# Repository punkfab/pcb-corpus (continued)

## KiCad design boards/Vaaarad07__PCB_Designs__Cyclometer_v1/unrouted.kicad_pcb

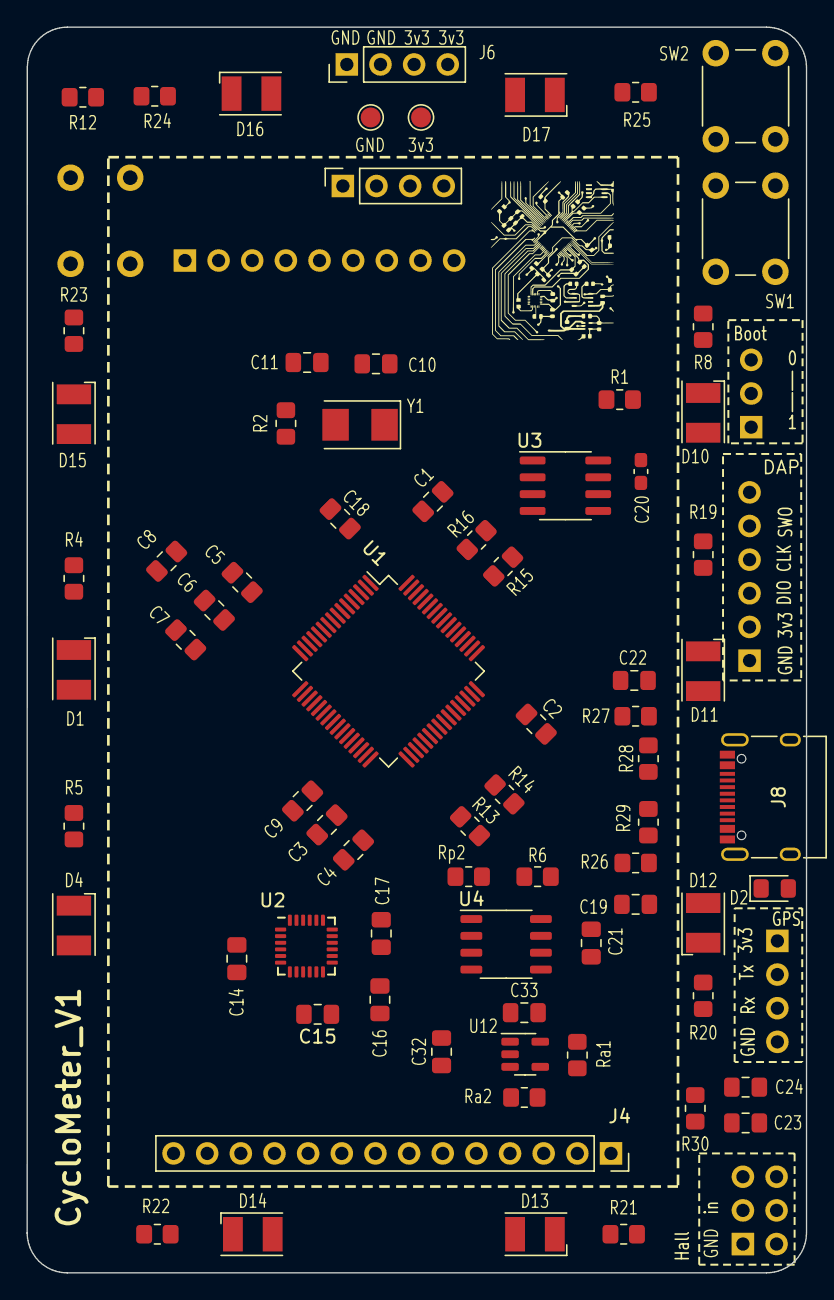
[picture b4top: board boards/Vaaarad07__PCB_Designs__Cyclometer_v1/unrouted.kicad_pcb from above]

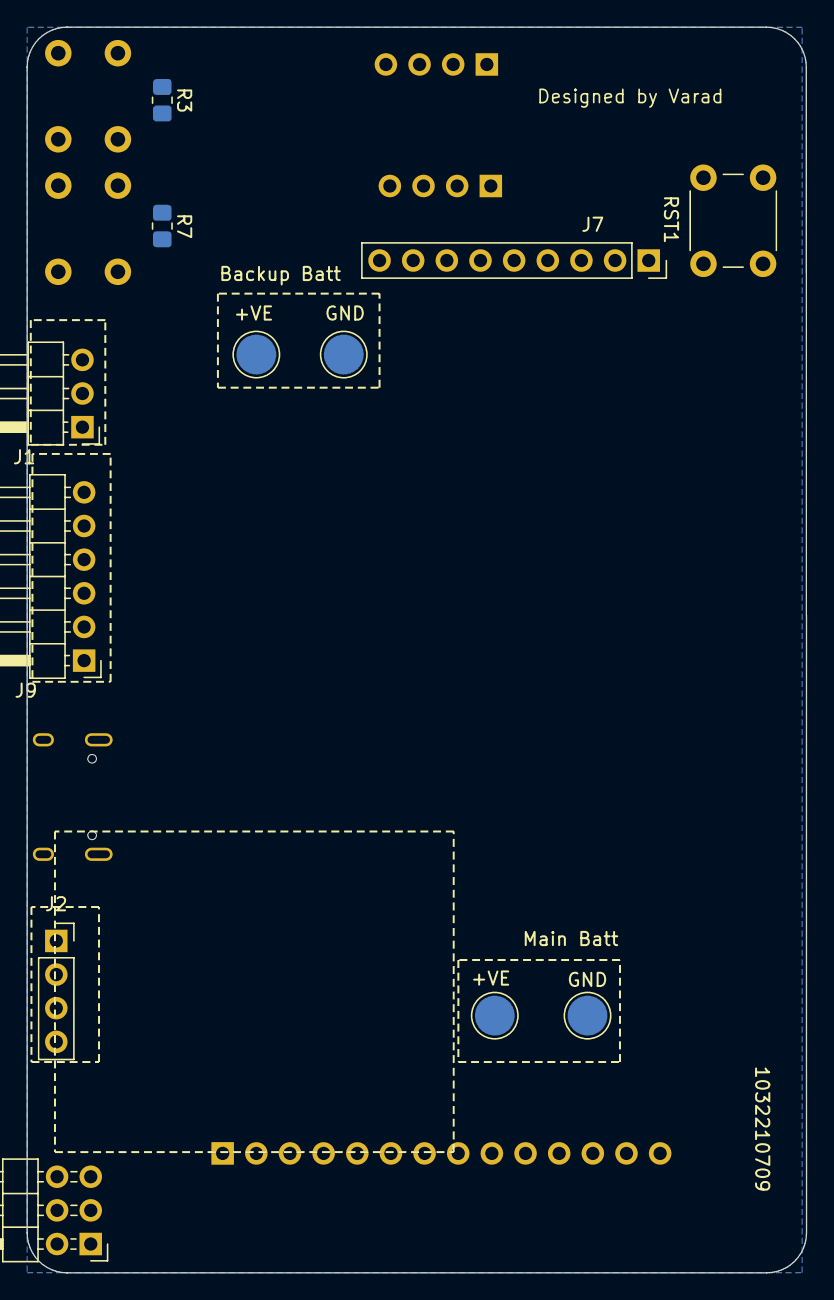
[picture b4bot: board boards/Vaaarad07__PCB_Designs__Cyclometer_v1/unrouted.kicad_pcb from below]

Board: 2 copper layers, 58.8 x 94.0 mm, 87 parts (12 on the bottom side), 66 nets, no tracks yet.

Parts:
C1, C2, C3, C4, C5, C6, C8: 100nF; C_0805_2012Metric_Pad1.18x1.45mm_HandSolder
C7: 1uF; C_0805_2012Metric_Pad1.18x1.45mm_HandSolder
C9: 4.7uF; C_0805_2012Metric_Pad1.18x1.45mm_HandSolder
C10, C11: TBC; C_0805_2012Metric_Pad1.18x1.45mm_HandSolder
C14: 10nF; C_0805_2012Metric_Pad1.18x1.45mm_HandSolder
C15, C16, C19, C24: 0.1uF; C_0805_2012Metric_Pad1.18x1.45mm_HandSolder
C17: 2.2nF; C_0805_2012Metric_Pad1.18x1.45mm_HandSolder
C18, C21, C22, C23, C32, C33: 10uF; C_0805_2012Metric_Pad1.18x1.45mm_HandSolder
C20: 100nF; C_0603_1608Metric_Pad1.08x0.95mm_HandSolder
D1, D4, D10, D11, D12, D13, D14, D15, D16, D17: LED; LED_PLCC-2_3.4x3.0mm_KA
D2: LED; LED_0805_2012Metric_Pad1.15x1.40mm_HandSolder
J1: Conn_01x03_Male; PinHeader_1x03_P2.54mm_Horizontal
J2: GPS; PinSocket_1x04_P2.54mm_Vertical
J3: Conn_01x06_Pin; PinHeader_2x03_P2.54mm_Horizontal
J4: LCD; PinSocket_1x14_P2.54mm_Vertical
J5: LCD; PinSocket_1x04_P2.54mm_Vertical
J6: PinHeader_1x04_P2.54mm_Vertical
J7: NRF; PinSocket_1x09_P2.54mm_Vertical
J8: USB_C_Receptacle; USB_C_Receptacle_XKB_U262-16XN-4BVC11
J9: Conn_01x06_Pin; PinHeader_1x06_P2.54mm_Horizontal
R1, R3, R4, R5, R7, R8, R12, R19, R20, R21, R22, R23, R24, R25, R30: 10K; R_0805_2012Metric_Pad1.20x1.40mm_HandSolder
R2: TBC; R_0805_2012Metric_Pad1.20x1.40mm_HandSolder
R6: R_Small_US; R_0805_2012Metric_Pad1.20x1.40mm_HandSolder
R13, R14, R15, R16: 4.7k; R_0805_2012Metric_Pad1.20x1.40mm_HandSolder
R26, R27, R28, R29: 5.1k; R_0805_2012Metric_Pad1.20x1.40mm_HandSolder
RST1: SW_Push; SW_PUSH_6mm
Ra1, Ra2: R_Small_US; R_0805_2012Metric_Pad1.20x1.40mm_HandSolder
Rp2: 1K2; R_0805_2012Metric_Pad1.20x1.40mm_HandSolder
SW1, SW2: SW_Push; SW_PUSH_6mm
TP1, TP4: +VE; TestPoint_Pad_D3.0mm
TP2, TP3: GND; TestPoint_Pad_D3.0mm
TP5: GND; TestPoint_Pad_D1.5mm
TP6: 3v3; TestPoint_Pad_D1.5mm
U1: STM32F446RCTx; LQFP-64_10x10mm_P0.5mm
U2: MPU-6050; InvenSense_QFN-24_4x4mm_P0.5mm
U3: AT24CS32-SSHM; SOIC-8_3.9x4.9mm_P1.27mm
U4: TP4056; SOP-8_3.9x4.9mm_P1.27mm
U12: LDK130-ADJ_SOT23_SOT353; SOT-23-5
Y1: Crystal; Crystal_SMD_5032-2Pin_5.0x3.2mm

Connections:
+3.3V: C1.1, C2.1, C3.1, C4.1, C5.1, C6.1, C7.1, C16.2, C20.2, C23.2, C24.1, C33.2, D1.2 (A), D4.2 (A), D10.2 (A), D11.2 (A), D12.2 (A), D13.2 (A), D14.2 (A), D15.2 (A), D16.2 (A), D17.2 (A), J1.1, J2.1, J4.7, J4.14, J6.3, J6.4, J7.8, J9.2, R3.2, R7.2, R12.2, R13.2, R14.2, R15.2, R16.2, R28.2, R29.2, R30.2, Ra1.1, TP6.1, U1.13 (VDDA), U1.19 (VDD), U1.32 (VDD), U1.48 (VDD), U1.64 (VDD), U2.13 (VDD), U3.8 (VCC), U12.5 (OUT)
/MCU/EEPROM_SCL_1: R15.1, U1.58 (PB6), U3.6 (SCL)
/MCU/EEPROM_SDA_1: R16.1, U1.59 (PB7), U3.5 (SDA)
/MCU/GPS_1_Rx: J2.3, U1.38 (PC7)
/MCU/GPS_1_Tx: J2.2, U1.37 (PC6)
/MCU/HSE_IN: C10.1, U1.5 (PH0), Y1.1
/MCU/HSE_OUT: R2.2, U1.6 (PH1)
/MCU/HallEffect_ip: J3.3, J3.4, R30.1, U1.35 (PB14)
/MCU/IMU_SCL: R14.1, U1.41 (PA8), U2.23 (SCL)
/MCU/IMU_SDA: R13.1, U1.40 (PC9), U2.24 (SDA)
/MCU/LCD_Cs: J4.12, U1.16 (PA2)
/MCU/LCD_DcRs: J4.10, U1.20 (PA4)
/MCU/LCD_Miso: J4.6, U1.22 (PA6)
/MCU/LCD_Mosi: J4.9, U1.23 (PA7)
/MCU/LCD_Sck: J4.8, U1.21 (PA5)
/MCU/LCD_rst: J4.11, U1.17 (PA3)
/MCU/LED1: R8.1, U1.53 (PC12)
/MCU/LED2: R19.1, U1.42 (PA9)
/MCU/LED3: R20.1, U1.36 (PB15)
/MCU/LED4: R21.1, U1.33 (PB12)
/MCU/LED5: R22.1, U1.27 (PB1)
/MCU/LED8: R23.1, U1.3 (PC14)
/MCU/LED9: R24.1, U1.62 (PB9)
/MCU/LED10: R25.1, U1.61 (PB8)
/MCU/NRF_MISO_2: J7.5, U1.10 (PC2)
/MCU/NRF_MOSI2: J7.6, U1.9 (PC1)
/MCU/NRF_RDYN: J7.4, U1.11 (PC3)
/MCU/NRF_REQN: J7.7, U1.8 (PC0)
/MCU/NRF_SCK2: J7.1, U1.29 (PB10)
/MCU/NRF_UART_RX: J7.2, R5.1, U1.15 (PA1)
/MCU/NRF_UART_TX: J7.3, R4.1, U1.14 (PA0)
/MCU/SWCLK: J9.4, U1.49 (PA14)
/MCU/SWDIO: J9.3, U1.46 (PA13)
/MCU/SWO: J9.5, U1.55 (PB3)
/MCU/user_1: R7.1, SW1.1, U1.51 (PC10)
/MCU/user_2: R3.1, SW2.1, U1.56 (PB4)
/Power/USB_CC1: J8.B5 (CC2), R27.2
/Power/USB_CC2: J8.A5 (CC1), R26.2
Batt+: C21.1, C32.1, TP1.1, U4.5 (BAT), U12.1 (IN), U12.3 (EN)
GND: C1.2, C2.2, C3.2, C4.2, C5.2, C6.2, C7.2, C8.2, C9.2, C10.2, C11.2, C14.1, C15.1, C16.1, C17.1, C18.1, C19.2, C20.1, C21.2, C22.2, C23.1, C24.2, C32.2, C33.1, J1.3, J2.4, J3.1, J3.2, J3.5, J3.6, J4.13, J5.1, J5.2, J5.3, J5.4, J6.1, J6.2, J7.9, J8.A1 (GND), J8.A12 (GND), J8.B1 (GND), J8.B12 (GND), J8.S1 (SHIELD), J9.1, J9.6, R26.1, R27.1, RST1.1, Ra2.2, Rp2.1, SW1.2, SW2.2, TP2.1, TP3.1, TP5.1, U1.12 (VSSA), U1.18 (VSS), U1.31 (VSS), U1.47 (VSS), U1.63 (VSS), U2.18 (GND), U3.4 (GND), U3.7 (WP), U4.1 (Temp1), U4.3 (GND3), U12.2 (GND)
unnamed: C11.1, R2.1, Y1.2
unnamed: D1.1 (K), R4.2
unnamed: C19.1, C22.1, D2.2 (A), J8.A4 (VBUS), J8.A9 (VBUS), J8.B4 (VBUS), J8.B9 (VBUS), U4.4 (Vcc4), U4.8 (CE)
unnamed: D2.1 (K), R6.1
unnamed: D4.1 (K), R5.2
unnamed: D10.1 (K), R8.2
unnamed: D11.1 (K), R19.2
unnamed: D12.1 (K), R20.2
unnamed: D13.1 (K), R21.2
unnamed: D14.1 (K), R22.2
unnamed: D15.1 (K), R23.2
unnamed: D16.1 (K), R24.2
unnamed: D17.1 (K), R25.2
unnamed: J1.2, R1.1
unnamed: R1.2, U1.60 (BOOT0)
unnamed: C8.1, R12.1, RST1.2, U1.7 (NRST)
unnamed: C9.1, U1.30 (VCAP_1)
unnamed: C17.2, U2.20 (CPOUT)
unnamed: C15.2, U2.10 (REGOUT)
unnamed: C14.2, U2.8 (VLOGIC)
unnamed: R6.2, U4.7 (CHRG)
unnamed: Rp2.2, U4.2 (prog2)
unnamed: Ra1.2, Ra2.1, U12.4 (ADJ)
USB_FS_D+: J8.A6 (D+), J8.B6 (D+), R28.1, U1.45 (PA12)
USB_FS_D-: J8.A7 (D-), J8.B7 (D-), R29.1, U1.44 (PA11)
Vbat: C18.2, TP4.1, U1.1 (VBAT)

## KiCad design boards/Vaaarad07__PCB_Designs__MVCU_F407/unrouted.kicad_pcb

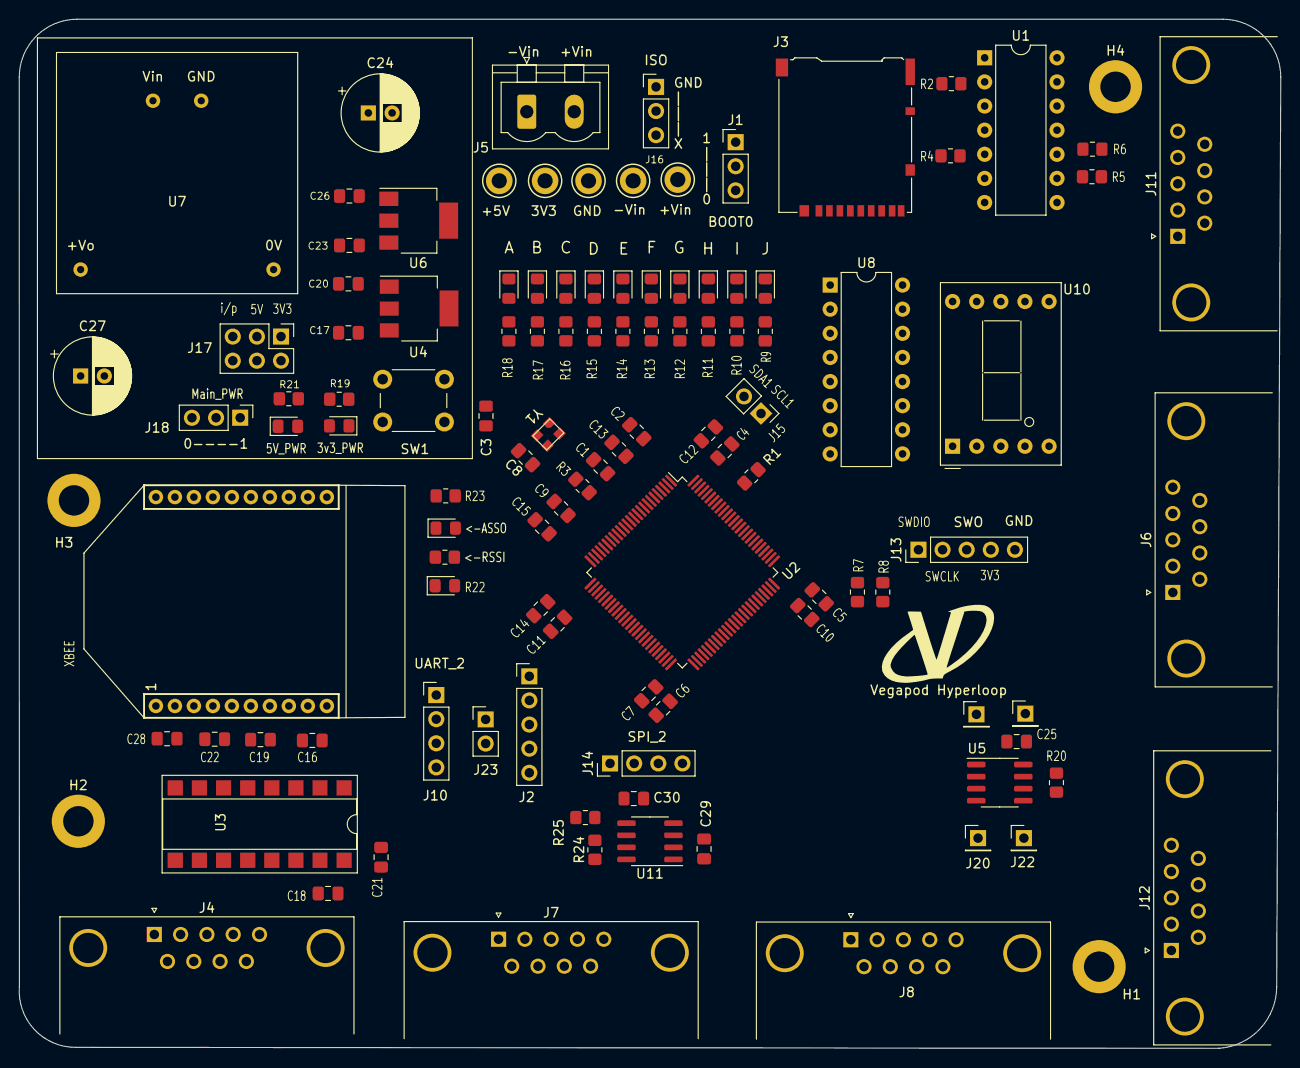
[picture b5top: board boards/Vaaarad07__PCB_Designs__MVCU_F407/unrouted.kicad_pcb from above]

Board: 4 copper layers, 132.8 x 108.4 mm, 113 parts (0 on the bottom side), 109 nets, no tracks yet.

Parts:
3V3: TestPoint; TestPoint_Keystone_5010-5014_Multipurpose
+5V: TestPoint; TestPoint_Keystone_5010-5014_Multipurpose
+Vin: TestPoint; TestPoint_Keystone_5010-5014_Multipurpose
-Vin: TestPoint; TestPoint_Keystone_5010-5014_Multipurpose
C1, C8: 12p; C_0805_2012Metric_Pad1.18x1.45mm_HandSolder
C2, C17, C20, C23, C26, C29, C30: 10uF; C_0805_2012Metric_Pad1.18x1.45mm_HandSolder
C3, C4, C5, C6, C9, C11, C12, C13, C14: 100nF; C_0805_2012Metric_Pad1.18x1.45mm_HandSolder
C7, C10: 2.2uF; C_0805_2012Metric_Pad1.18x1.45mm_HandSolder
C15, C25: 1uF; C_0805_2012Metric_Pad1.18x1.45mm_HandSolder
C16, C18, C19, C21, C22, C28: 0.1uF; C_0805_2012Metric_Pad1.18x1.45mm_HandSolder
C24: 100uF; CP_Radial_D8.0mm_P2.50mm
C27: 10uF; CP_Radial_D8.0mm_P2.50mm
D1, D2, D3, D4, D5, D6, D7, D8, D9, D10, D11, D12, D13, D14: LED; LED_0805_2012Metric_Pad1.15x1.40mm_HandSolder
GND: TestPoint; TestPoint_Keystone_5010-5014_Multipurpose
H1, H2, H3, H4: MountingHole_Pad; MountingHole_3.2mm_M3_DIN965_Pad
J1, J16, J18: Conn_01x03_Male; PinHeader_1x03_P2.54mm_Vertical
J2: Conn_01x05_Male; PinHeader_1x05_P2.54mm_Vertical
J3: Micro_SD_Card_Det_Hirose_DM3AT; microSD_HC_Hirose_DM3AT-SF-PEJM5
J4: IMU; DSUB-9_Male_Horizontal_P2.77x2.84mm_EdgePinOffset7.70mm_Hou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
J5: Conn_01x02_Male; PhoenixContact_MSTBVA_2,5_2-G_1x02_P5.00mm_Vertical
J6, J7, J8, J11, J12: DB9_Male_MountingHoles; DSUB-9_Male_Horizontal_P2.77x2.84mm_EdgePinOffset7.70mm_Hou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
J10, J14: Uart; PinHeader_1x04_P2.54mm_Vertical
J13: SWD; PinHeader_1x05_P2.54mm_Vertical
J15, J23: Conn_01x02_Male; PinHeader_1x02_P2.54mm_Vertical
J17: Conn_02x03_Counter_Clockwise; PinHeader_2x03_P2.54mm_Vertical
J19, J20, J21, J22: Conn_01x01_Male; PinHeader_1x01_P2.54mm_Vertical
R1: 10K; R_0805_2012Metric_Pad1.20x1.40mm_HandSolder
R2, R4, R5, R6: 3.3k; R_0805_2012Metric_Pad1.20x1.40mm_HandSolder
R3: R_Small_US; R_0805_2012Metric_Pad1.20x1.40mm_HandSolder
R7, R8, R9, R10, R11, R12, R13, R14, R15, R16, R17, R18, R19, R21, R22, R23: 1K; R_0805_2012Metric_Pad1.20x1.40mm_HandSolder
R20: 120R; R_0805_2012Metric_Pad1.20x1.40mm_HandSolder
R24, R25: 1.5k; R_0805_2012Metric_Pad1.20x1.40mm_HandSolder
SW1: SW_Push; SW_PUSH_6mm_H5mm
U1: 74LS125; DIP-14_W7.62mm
U2: STM32F407VGTx; LQFP-100_14x14mm_P0.5mm
U3: MAX232; DIP-16_W7.62mm_SMDSocket_SmallPads
U4: AMS1117-3.3; SOT-223-3_TabPin2
U5: MCP2551-I-SN; SOIC-8_3.9x4.9mm_P1.27mm
U6: AMS1117-5.0; SOT-223-3_TabPin2
U7: MORNSUN-URB2405YMD-6WR3
U8: 74LS47; DIP-16_W7.62mm
U9: XB24CDMPIT-001; XBEE
U10: D168K; D1X8K
U11: ACS712xLCTR-20A; SOIC-8_3.9x4.9mm_P1.27mm
Y1: Crystal_GND24; crystal

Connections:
+3.3V: 3V3.1, C2.1, C4.1, C5.1, C6.1, C9.1, C11.1, C12.1, C13.1, C14.1, C15.1, C20.1, C28.1, J1.1, J3.4 (VDD), J13.4, J17.2, R7.1, R8.1, R19.2, U1.14 (VCC), U2.6 (VBAT), U2.11 (VDD), U2.19 (VDD), U2.21 (VREF+), U2.22 (VDDA), U2.28 (VDD), U2.50 (VDD), U2.75 (VDD), U2.100 (VDD), U4.2 (VO), U9.1
+5V: +5V.1, C17.1, C18.1, C21.1, C25.1, C29.1, J6.9, J7.9, J8.9, J11.9, J12.9, J17.4, J18.1, U3.16 (VCC), U4.3 (VI), U5.3 (VDD), U8.16 (VCC), U11.1 (IP+), U11.2 (IP+), U11.8 (VCC)
/ADC_in6: J2.1, U2.31 (PA6)
/ADC_in7: J2.2, U2.32 (PA7)
/ADC_in8: J2.5, U2.35 (PB0)
/ADC_in9: R24.2, R25.1, U2.36 (PB1)
/ADC_in14: J2.3, U2.33 (PC4)
/ADC_in15: J2.4, U2.34 (PC5)
/BOOT0: R1.2, U2.94 (BOOT0)
/C13: R16.2, U2.7 (PC13)
/C14: R17.2, U2.8 (PC14)
/C15: R18.2, U2.9 (PC15)
/CAN_N: J6.2, J7.2, J8.2, J11.2, J12.2, J22.1, R20.2, U5.6 (CANL)
/CAN_P: J6.7, J7.7, J8.7, J11.7, J12.7, J21.1, R20.1, U5.7 (CANH)
/CAN_Rx: J20.1, U2.70 (PA11), U5.4 (RXD)
/CAN_Tx: J19.1, U2.71 (PA12), U5.1 (TXD)
/CS_LLS: J3.2 (DAT3/CD), U1.8
/DAC_1: J23.1, U2.29 (PA4)
/DAC_2: J23.2, U2.30 (PA5)
/DI_LLS: J3.3 (CMD), U1.3
/DO_LLS: J3.7 (DAT0), R6.2
/E0: R9.2, U2.97 (PE0)
/E1: R10.2, U2.98 (PE1)
/E2: R11.2, U2.1 (PE2)
/E3: R12.2, U2.2 (PE3)
/E4: R13.2, U2.3 (PE4)
/E5: R14.2, U2.4 (PE5)
/E6: R15.2, U2.5 (PE6)
/HSE_IN: C1.2, U2.12 (PH0), Y1.1
/HSE_OUT: R3.1, U2.13 (PH1)
/I2C1_SCL: J15.1, U2.95 (PB8)
/I2C1_SDA: J15.2, U2.96 (PB9)
/I2C3_SCL: J6.4, J7.4, J8.4, J11.4, J12.4, R8.2, U2.67 (PA8)
/I2C_SDA: J6.8, J7.8, J8.8, J11.8, J12.8, R7.2, U2.66 (PC9)
/IMU_Rx: U2.48 (PB11), U3.12 (R1OUT)
/IMU_Tx: U2.47 (PB10), U3.11 (T1IN)
/MVCU_HBT: J6.1, J7.1, J8.1, J11.1, J12.1, U2.61 (PD14)
/RSSI: R22.2, U2.42 (PE11), U9.6
/RST: U2.39 (PE8), U9.5
/Rx: J4.2, U3.14 (T1OUT)
/SCK_LLS: J3.5 (CLK), U1.6
/SD_CS: R5.2, U2.77 (PA15)
/SD_MISO: U1.11, U2.79 (PC11)
/SD_MOSI: R2.2, U2.80 (PC12)
/SD_SCK: R4.2, U2.78 (PC10)
/SPI2_MISO: J14.2, U2.53 (PB14)
/SPI2_MOSI: J14.3, U2.54 (PB15)
/SPI2_SCK: J14.1, U2.52 (PB13)
/SWCLK: J13.2, U2.76 (PA14)
/SWDIO: J13.1, U2.72 (PA13)
/SWo: J13.3, U2.89 (PB3)
/Tx: J4.3, U3.13 (R1IN)
/USART2_Rx: J10.2, U2.26 (PA3)
/USART2_Tx: J10.1, U2.25 (PA2)
/VCU1_HBT: J11.6, U2.60 (PD13)
/VCU2_HBT: J6.6, U2.59 (PD12)
/VCU3_HBT: J12.6, U2.58 (PD11)
/VCU4_HBT: J8.6, U2.57 (PD10)
/VCU5_HBT: J7.6, U2.56 (PD9)
/Xbee_Rx: U2.23 (PA0), U9.3
/Xbee_Tx: U2.24 (PA1), U9.2
/display_a: U2.82 (PD1), U8.7 (A)
/display_b: U2.83 (PD2), U8.1 (B)
/display_c: U2.84 (PD3), U8.2 (C)
/display_d: U2.85 (PD4), U8.6 (D)
/gpio: J10.3, U2.44 (PE13)
/mornsun_Vin: +Vin.1, C23.1, C24.1, J5.2, J17.6, U6.3 (VI), U7.2 (Vin)
/mornsun_minus: -Vin.1, J5.1, J16.2, U7.1 (GND)
GND: C1.1, C2.2, C3.2, C4.2, C5.2, C6.2, C7.1, C8.1, C9.2, C10.1, C11.2, C12.2, C13.2, C14.2, C15.2, C17.2, C18.2, C20.2, C22.1, C23.2, C24.2, C25.2, C26.2, C27.1, C28.2, C29.2, C30.2, D1.1 (K), D2.1 (K), D3.1 (K), D4.1 (K), D5.1 (K), D6.1 (K), D7.1 (K), D8.1 (K), D9.1 (K), D10.1 (K), D11.1 (K), D12.1 (K), D13.1 (K), D14.1 (K), GND.1, H1.1, H2.1, H3.1, H4.1, J1.3, J3.6 (VSS), J3.11 (SHIELD), J4.0 (PAD), J4.5, J6.0 (PAD), J6.3, J6.5, J7.0 (PAD), J7.3, J7.5, J8.0 (PAD), J8.3, J8.5, J10.4, J11.0 (PAD), J11.3, J11.5, J12.0 (PAD), J12.3, J12.5, J13.5, J14.4, J16.1, J17.1, J17.3, J17.5, R25.2, SW1.1, U1.1, U1.4, U1.7 (GND), U1.10, U1.13, U2.10 (VSS), U2.20 (VSSA), U2.27 (VSS), U2.74 (VSS), U2.99 (VSS), U3.15 (GND), U4.1 (GND), U5.2 (VSS), U5.8 (Rs), U6.1 (GND), U7.4 (0V), U8.8 (GND), U9.10, U10.3 (CC), U10.8 (CC), U11.3 (IP-), U11.4 (IP-), U11.5 (GND), Y1.2, Y1.4
unnamed: C3.1, SW1.2, U2.14 (NRST)
unnamed: C7.2, U2.49 (VCAP_1)
unnamed: C8.2, R3.2, Y1.3
unnamed: C10.2, U2.73 (VCAP_2)
unnamed: C16.1, U3.3 (C1-)
unnamed: C16.2, U3.1 (C1+)
unnamed: C19.1, U3.5 (C2-)
unnamed: C19.2, U3.4 (C2+)
unnamed: C21.2, U3.2 (VS+)
unnamed: C22.2, U3.6 (VS-)
unnamed: C26.1, C27.2, J18.2, R21.2, U6.2 (VO), U7.3 (+Vo)
unnamed: C30.1, U11.6 (FILTER)
unnamed: D1.2 (A), R9.1
unnamed: D2.2 (A), R10.1
unnamed: D3.2 (A), R11.1
unnamed: D4.2 (A), R12.1
unnamed: D5.2 (A), R13.1
unnamed: D6.2 (A), R14.1
unnamed: D7.2 (A), R15.1
unnamed: D8.2 (A), R16.1
unnamed: D9.2 (A), R17.1
unnamed: D10.2 (A), R18.1
unnamed: D11.2 (A), R19.1
unnamed: D12.2 (A), R21.1
unnamed: D13.2 (A), R22.1
unnamed: D14.2 (A), R23.1
unnamed: J1.2, R1.1
unnamed: R2.1, U1.2
unnamed: R4.1, U1.5
unnamed: R5.1, U1.9
unnamed: R6.1, U1.12
unnamed: R23.2, U9.15
unnamed: R24.1, U11.7 (VIOUT)
unnamed: U8.9 (e), U10.1 (E)
unnamed: U8.10 (d), U10.2 (D)
unnamed: U8.11 (c), U10.4 (C)
unnamed: U8.12 (b), U10.6 (B)
unnamed: U8.13 (a), U10.7 (A)
unnamed: U8.15 (f), U10.9 (F)
unnamed: U8.14 (g), U10.10 (G)
